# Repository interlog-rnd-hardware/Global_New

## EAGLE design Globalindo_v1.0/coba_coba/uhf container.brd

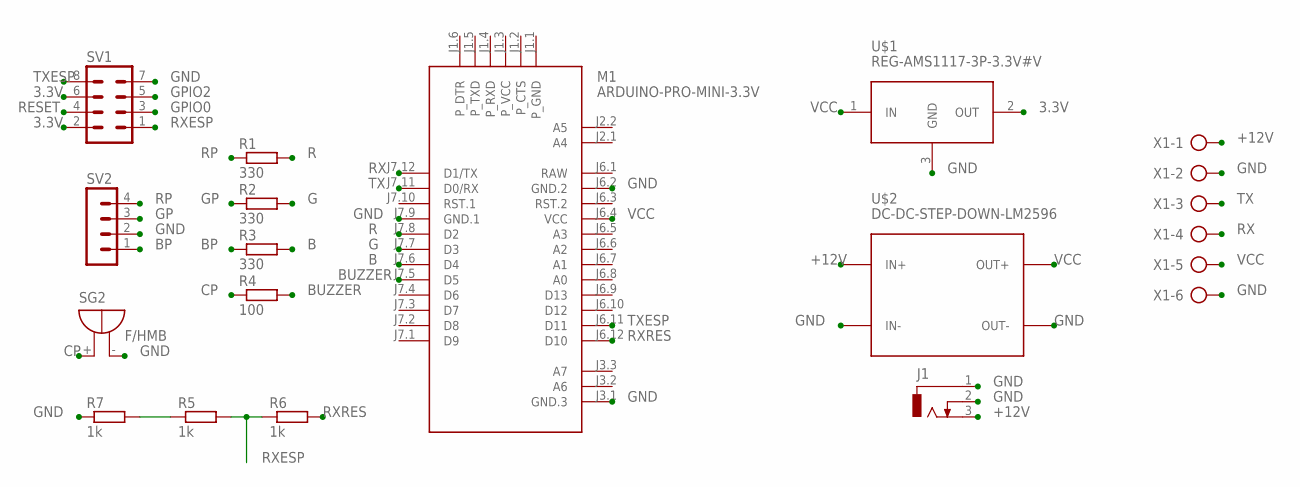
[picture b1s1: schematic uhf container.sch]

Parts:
J1: DCJ0303
M1: ARDUINO-PRO-MINI-3.3V; ARDUINO-PRO-MINI
R1, R2, R3: 330; 0207/7
R4: 100; 0207/7
R5, R6, R7: 1k; 0207/7
SG2: F/HMB
SV1: MA04-2
SV2: MA04-1
U$1: REG-AMS1117-3P-3.3V#V; REG-AMS1117-3P#V
U$2: DC-DC-STEP-DOWN-LM2596
X1: AK300/6

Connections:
3.3V: SV1.2, SV1.6, U$1.2 (OUT)
+12V: J1.3, U$2.IN+, X1.1
B: M1.J7.6 (D4), R3.2
BP: R3.1, SV2.1
BUZZER: M1.J7.5 (D5), R4.2
CP: R4.1, SG2.+
G: M1.J7.7 (D3), R2.2
GND: J1.1, J1.2, M1.J3.1 (GND.3), M1.J6.2 (GND.2), M1.J7.9 (GND.1), R7.1, SG2.-, SV1.7, SV2.2, U$1.3 (GND), U$2.IN-, U$2.OUT-, X1.2, X1.6
GP: R2.1, SV2.3
GPIO0: SV1.3
GPIO2: SV1.5
unnamed: R5.1, R7.2
R: M1.J7.8 (D2), R1.2
RAW: M1.J6.1 (RAW)
RESET: SV1.4
RP: R1.1, SV2.4
RX: M1.J7.12 (D1/TX), X1.4
RXESP: R5.2, R6.1, SV1.1
RXRES: M1.J6.12 (D10), R6.2
TX: M1.J7.11 (D0/RX), X1.3
TXESP: M1.J6.11 (D11), SV1.8
VCC: M1.J6.4 (VCC), U$1.1 (IN), U$2.OUT+, X1.5

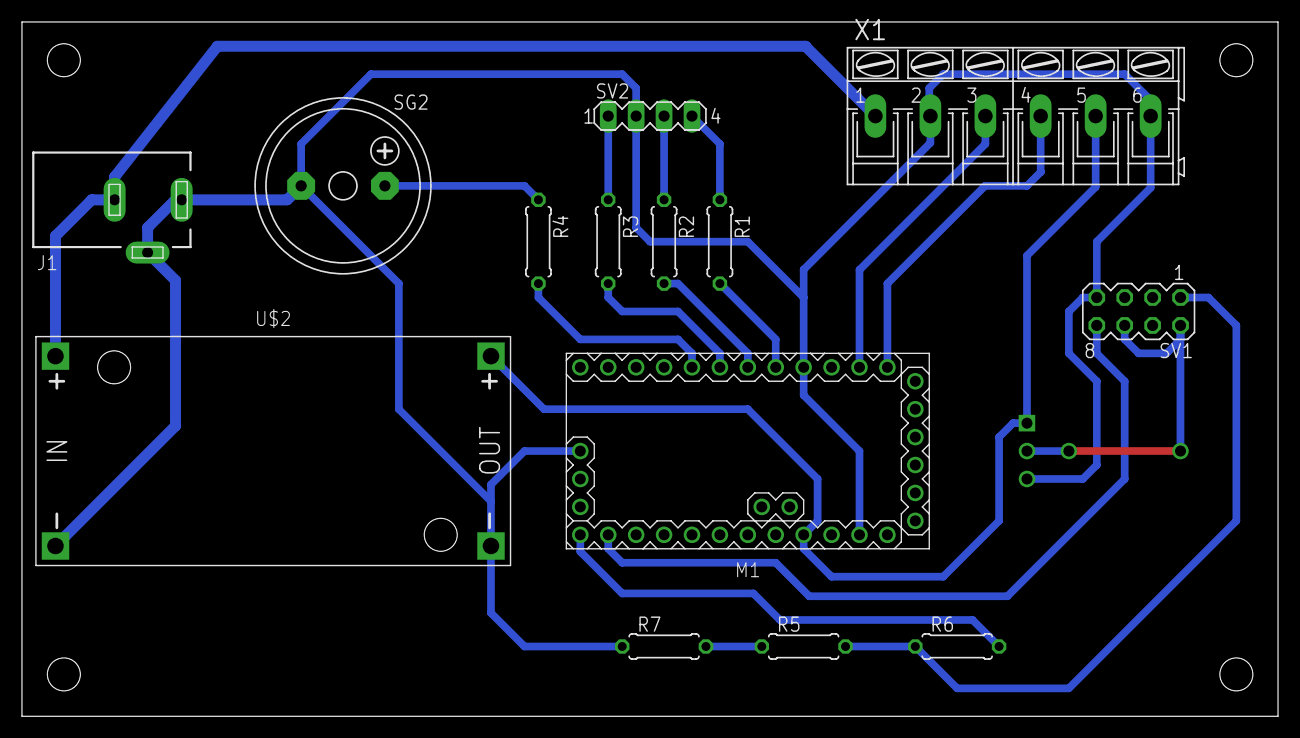
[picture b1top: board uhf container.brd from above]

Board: 2 copper layers, 114.3 x 63.2 mm, 15 parts (1 on the bottom side), 18 nets.

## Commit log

2020-04-30 Create upload_di_global_asli
2020-06-18 Add files via upload
    Beberapa fungsi yg dapat dipanggil
    1. Void Hitungan = konversi hitungan dari RFID UHF cardtek ke hitungan arduino yang kita inginkan
    2. Void kelompok = Memasukkan kelompok ke berapa dari kelipatan 80
    3. String getValue

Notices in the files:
parts and their libraries:
diy-modules: Released under the Creative Commons Attribution 4.0 International License: http://creativecommons.org/licenses/by/4.0
